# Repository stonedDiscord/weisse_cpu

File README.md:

# Die Weiße CPU

Dies ist ein Reverse-Engineering Projekt fuer die "Elektronische Steuereinheit" von adp.

```mermaid
graph LR
    4087-000101

    subgraph CPU_BLK["CPU"]
        C["8085A\nICB2\n74LS373 addr latch\n74LS245 data buf"]
    end

    subgraph ADEC["Address Decode"]
        D["74LS138 (ICH5)\nmem bank select\n\n74LS42 ×3\nI/O port select"]
    end

    subgraph MMAP["Memory Map"]
        M1["0x0000–0x3FFF\nSocket 1 · ICD6 27128  (16 KB)"]
        M2["0x4000–0x7FFF\nSocket 2 · ICE6 27128  (16 KB)"]
        M3["0x8000–0x8FFF\nSocket 3 · ICC5 2764  (8 KB, empty)"]
        M4["0x9000–0x900F\nRTC · ICA3 HD146818  (16 B, mem-mapped)"]
        M5["0xC000–0xFFFF\nSRAM · ICC6 CY62256  (32 KB chip)"]
    end

    subgraph IOMAP["I/O Map"]
        I1["0x50  8279 data\n0x51  8279 cmd"]
        I2["0x60–6F  8256 regs"]
        I3["0x70  coin ejector\n0x71  sound start\n0x72  tone note\n0x73  PPI ctrl"]
    end

    subgraph EXT["External"]
        E1["16× 7-seg display\nLamp matrix 8×8\nButton/coin matrix 8×8"]
        E2["Serial 4800 8N1\nreel stepper motor\nreel optical sensor"]
        E3["Coin ejector\nTone generator"]
    end

    C <--> D
    D <--> MMAP
    D <--> IOMAP
    I1 --- E1
    I2 --- E2
    I3 --- E3
```

Bei 4040 Platinen sind die IO Adressen anders verteilt:

| IO | Ports |
| ---- | ----------------|
| 0x70-0x73 | 8255: Auswerfer+Zähler+Sound |
| 0x80-0x81 | 8279: Lampen+Tasten |
| 0x90-0x9f | 8256: Timer+Seriell+Walzen |

Aus diesem Grund sind die Programme nicht mit beiden Platinen kompatibel.
Die Lampen und Timer würden ohne Anpassung nicht funktionieren.

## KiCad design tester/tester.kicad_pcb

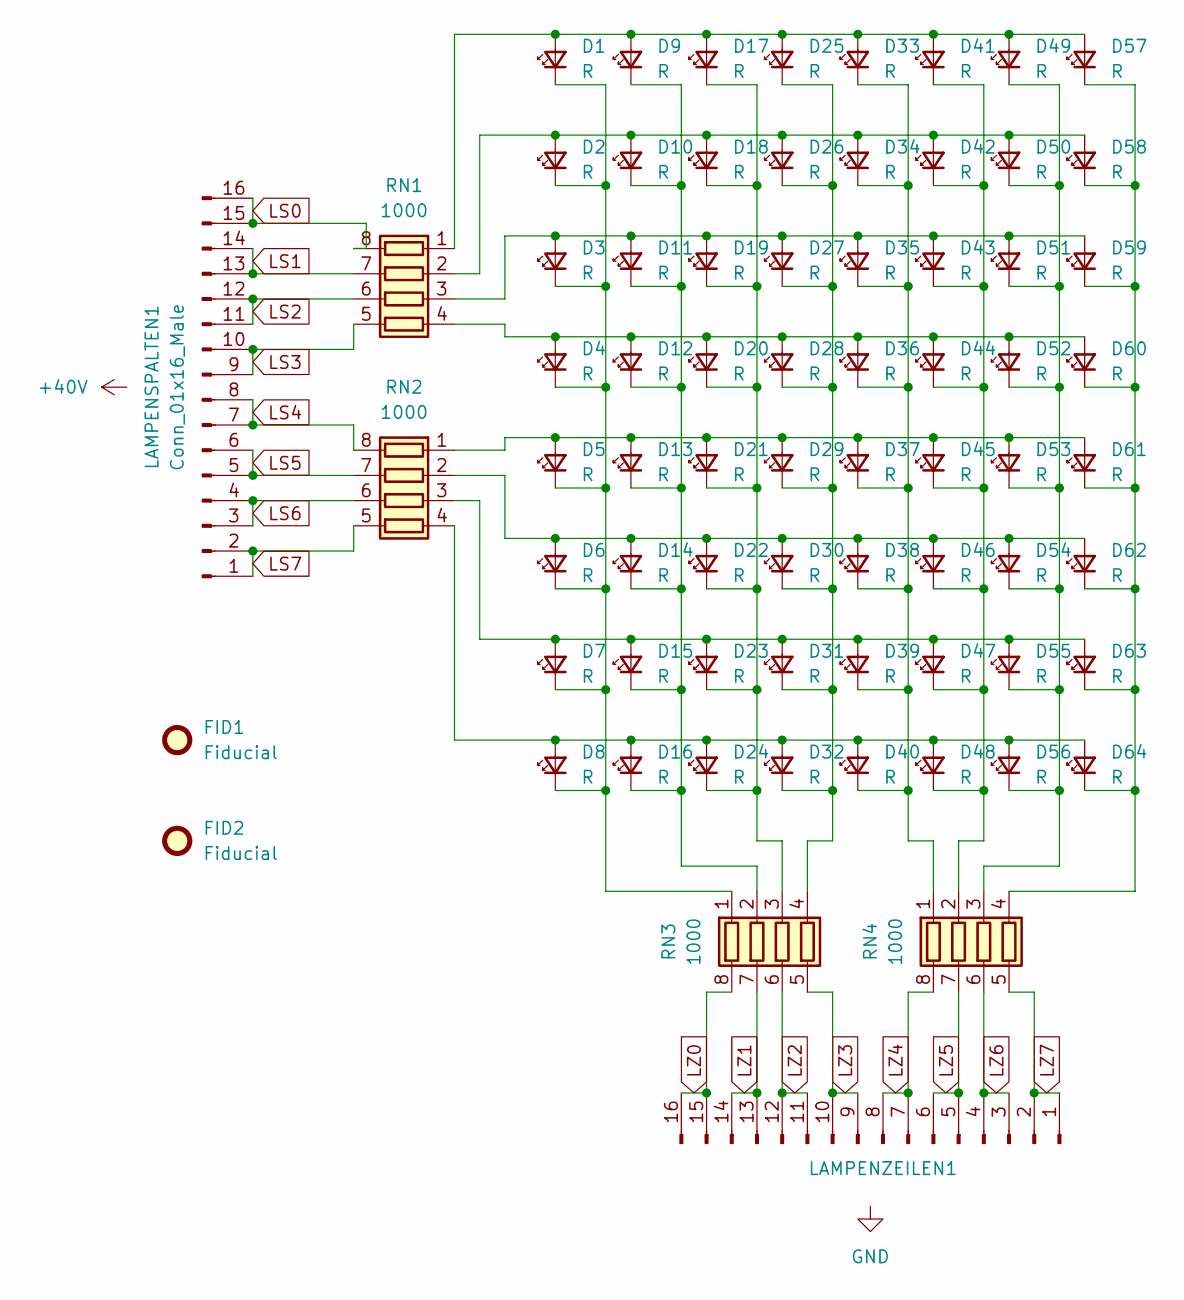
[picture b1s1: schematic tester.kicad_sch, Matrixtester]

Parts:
D1, D2, D3, D4, D5, D6, D7, D8, D9, D10, D11, D12, D13, D14, D15, D16, D17, D18, D19, D20, D21, D22, D23, D24, D25, D26, D27, D28, D29, D30, D31, D32, D33, D34, D35, D36, D37, D38, D39, D40, D41, D42, D43, D44, D45, D46, D47, D48, D49, D50, D51, D52, D53, D54, D55, D56, D57, D58, D59, D60, D61, D62, D63, D64: R; LED_0603_1608Metric_Pad1.05x0.95mm_HandSolder
FID1: Fiducial; Fiducial_Cross_1.5mm_Mask2mm
FID2: Fiducial; Fiducial_0.5mm_Mask1.5mm
LAMPENSPALTEN1: Conn_01x16_Male; Lumberg_MSF_B16B-MSF-A_1x16_P2.50mm_Vertical
LAMPENZEILEN1: Conn_01x16_Pin; Lumberg_MSF_B16B-MSF-A_1x16_P2.50mm_Vertical
RN1, RN2, RN3, RN4: 1000; R_Array_Concave_4x0603

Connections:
LS0: LAMPENSPALTEN1.15, LAMPENSPALTEN1.16, RN1.8 (R1.2)
LS1: LAMPENSPALTEN1.13, LAMPENSPALTEN1.14, RN1.7 (R2.2)
LS2: LAMPENSPALTEN1.11, LAMPENSPALTEN1.12, RN1.6 (R3.2)
LS3: LAMPENSPALTEN1.9, LAMPENSPALTEN1.10, RN1.5 (R4.2)
LS4: LAMPENSPALTEN1.7, LAMPENSPALTEN1.8, RN2.8 (R1.2)
LS5: LAMPENSPALTEN1.5, LAMPENSPALTEN1.6, RN2.7 (R2.2)
LS6: LAMPENSPALTEN1.3, LAMPENSPALTEN1.4, RN2.6 (R3.2)
LS7: LAMPENSPALTEN1.1, LAMPENSPALTEN1.2, RN2.5 (R4.2)
LZ0: LAMPENZEILEN1.15, LAMPENZEILEN1.16, RN3.8 (R1.2)
LZ1: LAMPENZEILEN1.13, LAMPENZEILEN1.14, RN3.7 (R2.2)
LZ2: LAMPENZEILEN1.11, LAMPENZEILEN1.12, RN3.6 (R3.2)
LZ3: LAMPENZEILEN1.9, LAMPENZEILEN1.10, RN3.5 (R4.2)
LZ4: LAMPENZEILEN1.7, LAMPENZEILEN1.8, RN4.8 (R1.2)
LZ5: LAMPENZEILEN1.5, LAMPENZEILEN1.6, RN4.7 (R2.2)
LZ6: LAMPENZEILEN1.3, LAMPENZEILEN1.4, RN4.6 (R3.2)
LZ7: LAMPENZEILEN1.1, LAMPENZEILEN1.2, RN4.5 (R4.2)
unnamed: D1.2 (A), D9.2 (A), D17.2 (A), D25.2 (A), D33.2 (A), D41.2 (A), D49.2 (A), D57.2 (A), RN1.1 (R1.1)
unnamed: D1.1 (K), D2.1 (K), D3.1 (K), D4.1 (K), D5.1 (K), D6.1 (K), D7.1 (K), D8.1 (K), RN3.1 (R1.1)
unnamed: D2.2 (A), D10.2 (A), D18.2 (A), D26.2 (A), D34.2 (A), D42.2 (A), D50.2 (A), D58.2 (A), RN1.2 (R2.1)
unnamed: D9.1 (K), D10.1 (K), D11.1 (K), D12.1 (K), D13.1 (K), D14.1 (K), D15.1 (K), D16.1 (K), RN3.2 (R2.1)
unnamed: D3.2 (A), D11.2 (A), D19.2 (A), D27.2 (A), D35.2 (A), D43.2 (A), D51.2 (A), D59.2 (A), RN1.3 (R3.1)
unnamed: D4.2 (A), D12.2 (A), D20.2 (A), D28.2 (A), D36.2 (A), D44.2 (A), D52.2 (A), D60.2 (A), RN1.4 (R4.1)
unnamed: D5.2 (A), D13.2 (A), D21.2 (A), D29.2 (A), D37.2 (A), D45.2 (A), D53.2 (A), D61.2 (A), RN2.1 (R1.1)
unnamed: D6.2 (A), D14.2 (A), D22.2 (A), D30.2 (A), D38.2 (A), D46.2 (A), D54.2 (A), D62.2 (A), RN2.2 (R2.1)
unnamed: D7.2 (A), D15.2 (A), D23.2 (A), D31.2 (A), D39.2 (A), D47.2 (A), D55.2 (A), D63.2 (A), RN2.3 (R3.1)
unnamed: D8.2 (A), D16.2 (A), D24.2 (A), D32.2 (A), D40.2 (A), D48.2 (A), D56.2 (A), D64.2 (A), RN2.4 (R4.1)
unnamed: D17.1 (K), D18.1 (K), D19.1 (K), D20.1 (K), D21.1 (K), D22.1 (K), D23.1 (K), D24.1 (K), RN3.3 (R3.1)
unnamed: D25.1 (K), D26.1 (K), D27.1 (K), D28.1 (K), D29.1 (K), D30.1 (K), D31.1 (K), D32.1 (K), RN3.4 (R4.1)
unnamed: D33.1 (K), D34.1 (K), D35.1 (K), D36.1 (K), D37.1 (K), D38.1 (K), D39.1 (K), D40.1 (K), RN4.1 (R1.1)
unnamed: D41.1 (K), D42.1 (K), D43.1 (K), D44.1 (K), D45.1 (K), D46.1 (K), D47.1 (K), D48.1 (K), RN4.2 (R2.1)
unnamed: D49.1 (K), D50.1 (K), D51.1 (K), D52.1 (K), D53.1 (K), D54.1 (K), D55.1 (K), D56.1 (K), RN4.3 (R3.1)
unnamed: D57.1 (K), D58.1 (K), D59.1 (K), D60.1 (K), D61.1 (K), D62.1 (K), D63.1 (K), D64.1 (K), RN4.4 (R4.1)

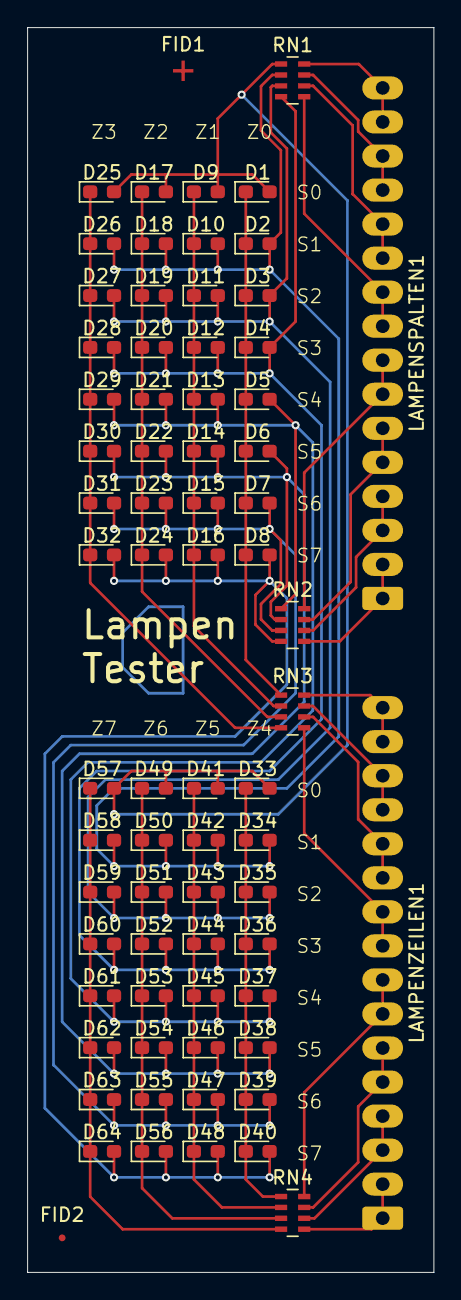
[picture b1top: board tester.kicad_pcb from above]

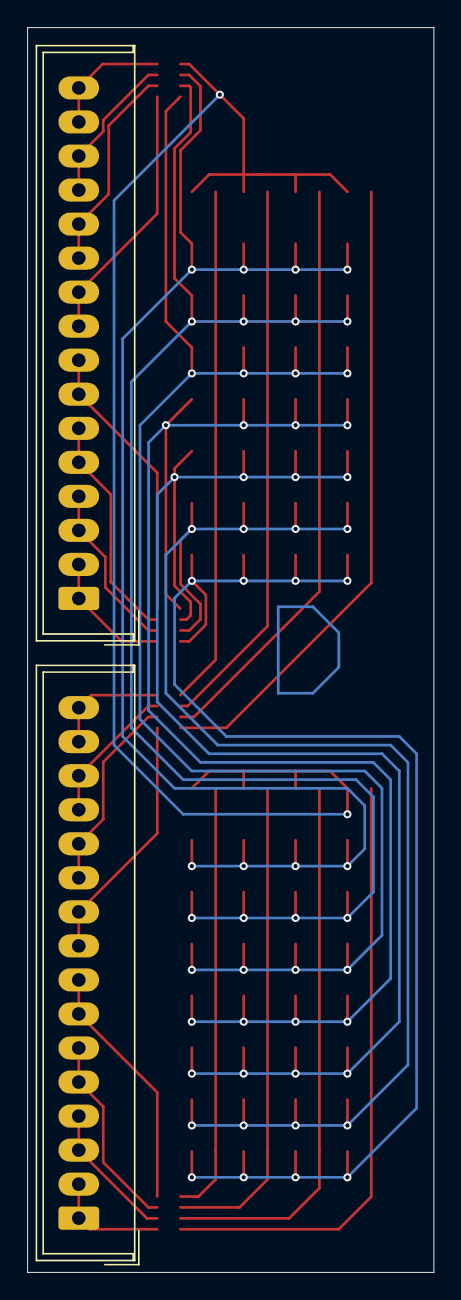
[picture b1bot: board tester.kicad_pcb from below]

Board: 2 copper layers, 29.8 x 91.4 mm, 72 parts (2 on the bottom side), 32 nets.

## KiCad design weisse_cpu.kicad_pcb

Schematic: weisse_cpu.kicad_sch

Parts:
AUSWERFER+SPERRMAG1: Conn_01x06_Pin; PinHeader_1x06_P2.54mm_Vertical
BATTERIE2: Battery_Cell; Batterie
C1, C76, C110, C130, C131, C159, C160, C161: C; C_Rect_L9.0mm_W2.5mm_P7.50mm_MKT
C2, C3, C49: C; CP_Radial_Tantal_D4.5mm_P2.50mm
C4, C5, C6, C7, C8, C9, C10, C11, C143, C144, C145, C146, C147, C148, C149, C150, C151, C152, C153, C154, C155, C156, C157, C158: C; C_Axial_L3.8mm_D2.6mm_P7.50mm_Horizontal
C20, C21, C22, C23, C24, C25, C26, C27: C; C_Rect_L7.0mm_W2.0mm_P5.00mm
C48: C; CP_Radial_Tantal_D4.5mm_P5.00mm
D1, D2, D4, D5, D6, D7, D8, D10, D11, D12, D13, D14, D15, D16, D17, D18, D19, D25, D26, D28, D29, D50, D51, D52, D73, D74, D75, D76, D77, D78, D79, D80, D81, D82, D83, D84, D85, D86, D87, D88, D89, D90, D91, D92, D93, D94, D95, D96, D97, D98, D99, D100, D101, D102, D103, D104, D105, D106, D107, D108, D109, D110, D111, D112: D; D_A-405_P7.62mm_Horizontal
D3, D27: D; BigDiode
DM1, DM2: DAN_801; SIP9_Housing
EINGAENGE1: Conn_01x08_Male; PinHeader_1x08_P2.54mm_Vertical
GONG1: Conn_01x02_Pin; PinHeader_1x02_P2.54mm_Vertical; not fitted
ICA2: LM324; DIP-14_W7.62mm
ICA3: PAL20L8; DIP-24_W15.24mm
ICA7: 4066; DIP-14_W7.62mm
ICA8: 40106; DIP-14_W7.62mm
ICA9: CNY17-1; DIP-6_W7.62mm
ICB2: 8085; DIP-40_W15.24mm
ICB4: 74LS245; DIP-20_W7.62mm
ICB5: 74LS373; DIP-20_W7.62mm
ICB8: ICM7555xP; DIP-8_W7.62mm
ICB9, ICB10: 4066; DIP-14_W7.62mm
ICC3: 74LS04; DIP-14_W7.62mm
ICC4: 74LS00; DIP-14_W7.62mm
ICC5: 2764; DIP-24_W15.24mm
ICC6: CXK5816PN-12L; DIP-24_W15.24mm
ICC8: 74LS42; DIP-16_W7.62mm
ICC10: 4066; DIP-14_W7.62mm
ICD3: 74LS257; DIP-16_W7.62mm
ICD4: 74LS244; DIP-20_W7.62mm
ICD6: 27128; DIP-28_W15.24mm
ICD8: CD4051B; DIP-16_W7.62mm
ICD10: 4066; DIP-14_W7.62mm
ICE2: 8256; DIP-40_W15.24mm
ICE4: 74125; DIP-14_W7.62mm
ICE5: 74LS42; DIP-16_W7.62mm
ICE6: 27128; DIP-28_W15.24mm
ICE10: 4066; DIP-14_W7.62mm
ICF2: LM324; DIP-14_W7.62mm
ICF3: 4028; DIP-16_W7.62mm
ICF4-2: 4013; DIP-14_W7.62mm
ICF5: 74LS42; DIP-16_W7.62mm
ICF8: CD4051B; DIP-16_W7.62mm
ICF10: 4066; DIP-14_W7.62mm
ICG1, ICG2, ICG4, ICG4-1: LM324; DIP-14_W7.62mm
ICG3: 4051; DIP-16_W7.62mm
ICG5: DIP-40_W15.24mm
ICG8-1: 74LS290; DIP-14_W7.62mm
ICG8-2: 4040; DIP-16_W7.62mm
ICG9: DIP-16_W7.62mm
ICG10-1, ICG10-2: 4066; DIP-14_W7.62mm
ICH1: 4098; DIP-16_W7.62mm
ICH2: LM324; DIP-14_W7.62mm
ICH3: 4040; DIP-16_W7.62mm
ICH4-1: ULN2004A; DIP-16_W7.62mm
ICH4-2: 4520; DIP-16_W7.62mm
ICH5: 74LS138; DIP-16_W7.62mm
ICH6: 74AHC273; DIP-20_W7.62mm
ICH8: CD74HC4067M; SOIC-24W_7.5x15.4mm_P1.27mm
ICH10: 4066; DIP-14_W7.62mm
ICJ5, ICJ6: 74AHC273; DIP-20_W7.62mm
ICK4: 4013; DIP-14_W7.62mm
ICK5, ICK6, ICK7, ICK8, ICK11: LM324; DIP-14_W7.62mm
ICL4, ICL6, ICL9: 4093; DIP-14_W7.62mm
ICL5, ICL7: LM324; DIP-14_W7.62mm
ICL8: 4013; DIP-14_W7.62mm
ICL10: NE556; DIP-14_W7.62mm
ICL11: Opamp_Quad; DIP-14_W7.62mm
LAMPENSPALTEN1: Conn_01x16_Male; PinHeader_1x16_P2.54mm_Vertical
LAMPENZEILEN1: Conn_01x16_Pin; PinHeader_1x16_P2.54mm_Vertical
LAUTSPRECHER1: Conn_01x06_Pin; PinHeader_1x06_P2.54mm_Vertical
LED1, LED2, LED3, LED4, LED5: LED; LED_D5.0mm
LEISTUNGSAUSGAENGE1: Conn_01x10_Pin; PinHeader_1x10_P2.54mm_Vertical; not fitted
LEISTUNGSNETZ1: Conn_01x08_Male; PinHeader_1x08_P2.54mm_Vertical
LEUCHTZIFFERNANZEIGE1: Conn_01x12_Pin; PinHeader_1x12_P2.54mm_Vertical
MATRIX-EINGAENGE1: Conn_01x06_Pin; PinHeader_1x06_P2.54mm_Vertical; not fitted
MUENZANNAHME1: Conn_01x20_Pin; PinHeader_1x20_P2.54mm_Vertical
Q1: Crystal; Crystal_AT310_D3.0mm_L10.0mm_Vertical
Q2: Crystal; Crystal_HC18-U_Vertical
R1, R2, R10, R11, R12, R13, R27, R28, R29: 1,2k 5%; R_Axial_DIN0414_L11.9mm_D4.5mm_P20.32mm_Horizontal
R3, R17: R; R_Axial_DIN0204_L3.6mm_D1.6mm_P7.62mm_Horizontal
R4, R5, R6, R7: R; R_Axial_DIN0207_L6.3mm_D2.5mm_P10.16mm_Horizontal
R15, R20, R21, R123: 1 kΩ ±5%; R_Axial_DIN0207_L6.3mm_D2.5mm_P10.16mm_Horizontal
R16, R86, R150: 100 kΩ ±5%; R_Axial_DIN0207_L6.3mm_D2.5mm_P10.16mm_Horizontal
R22, R84, R124: 10 kΩ ±5%; R_Axial_DIN0207_L6.3mm_D2.5mm_P10.16mm_Horizontal
R23: 320 kΩ ±5%; R_Axial_DIN0207_L6.3mm_D2.5mm_P10.16mm_Horizontal
R40: 15 2%; BigResistor
R41, R65, R66, R90, R100: R; BigResistor
R82: 3 kΩ ±5%; R_Axial_DIN0207_L6.3mm_D2.5mm_P10.16mm_Horizontal
R83: 180 Ω ±5%; R_Axial_DIN0207_L6.3mm_D2.5mm_P10.16mm_Horizontal
R85: 27 kΩ ±5%; R_Axial_DIN0207_L6.3mm_D2.5mm_P10.16mm_Horizontal
R121: 220 kΩ ±5%; R_Axial_DIN0207_L6.3mm_D2.5mm_P10.16mm_Horizontal
R122: 1 MΩ ±5%; R_Axial_DIN0207_L6.3mm_D2.5mm_P10.16mm_Horizontal
R129: 1 kΩ ±5%; R_Axial_DIN0309_L9.0mm_D3.2mm_P15.24mm_Horizontal
R130: 51; R_Axial_DIN0414_L11.9mm_D4.5mm_P20.32mm_Horizontal
R135: 100 ±5%; R_Axial_DIN0414_L11.9mm_D4.5mm_P20.32mm_Horizontal
R136, R137: 200 Ω ±5%; R_Axial_DIN0414_L11.9mm_D4.5mm_P20.32mm_Horizontal
R140: 220 Ω ±5%; R_Axial_DIN0207_L6.3mm_D2.5mm_P10.16mm_Horizontal
R148: 3,3M 5%; R_Axial_DIN0207_L6.3mm_D2.5mm_P10.16mm_Horizontal
RM2, RM20: R_Network04; R_Array_SIP5
RM3, RM5, RM7, RM11, RM12, RM13, RM21, RM50, RM56, RM57, RM58, RM66, RM80, RM82, RM84: R_Network08; R_Array_SIP9
RM4, RM6, RM8, RM10, RM81, RM83, RM85: R_Pack08; DIP-16_W7.62mm
RN1: R_Network08; R_Array_SIP9
SERIELLE_DATEN1: Conn_01x08_Pin; PinHeader_1x08_P2.54mm_Vertical
SERVICEANZEIGE+TASTATUR1: Conn_01x20_Male; PinHeader_1x20_P2.54mm_Vertical
SIGNALNETZ1: Conn_01x06_Male; PinHeader_1x06_P2.54mm_Vertical
SW1: SW_DIP_x04; SW_DIP_SPSTx04_Slide_9.78x12.34mm_W7.62mm_P2.54mm
TASTEN1: Conn_01x06_Pin; PinHeader_1x06_P2.54mm_Vertical
TR1, TR2, TR10, TR11, TR12, TR25, TR26: BDX34B; TO-220-3_Vertical
TR3, TR14, TR15, TR16, TR30, TR31, TR33, TR34, TR85: BC237; TO-92_Inline
TR13: BDX54C; TO-220-3_Vertical
TR27: BD140; TO-126-3_Vertical
TR29, TR65, TR66: BD139; TO-126-3_Vertical
TR32: BD679; TO-126-3_Vertical
TR40: BC557; TO-92_Inline
TR55, TR56, TR70, TR71, TR72, TR73, TR80, TR81, TR82, TR83, TR95, TR96, TR97: Q_NPN_Darlington_BCE; TO-220-3_Vertical
TR84, TR87: NMOS; BigTransistor
TR86: BC327; TO-92_Inline
TUERSCHALTER+SPIELZAEHLER1: Conn_01x04_Pin; PinHeader_1x04_P2.54mm_Vertical
TY1, TY2, TY5, TY6, TY7, TY8, TY15, TY16: TIC126; TO-220-3_Vertical
WALZENANSTEUERUNG1: Conn_01x20_Pin; PinHeader_1x20_P2.54mm_Vertical
ZUSATZTASTEN1: Conn_01x08_Pin; PinHeader_1x08_P2.54mm_Vertical
ZUSATZWALZEN1: Conn_01x12_Pin; PinHeader_1x12_P2.54mm_Vertical; not fitted

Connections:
+5V: LEUCHTZIFFERNANZEIGE1.3, SERIELLE_DATEN1.1, SERVICEANZEIGE+TASTATUR1.2, SIGNALNETZ1.5, SIGNALNETZ1.6
+12V: C161.1, EINGAENGE1.1, LAUTSPRECHER1.2, LEUCHTZIFFERNANZEIGE1.4, MUENZANNAHME1.4, SERIELLE_DATEN1.8, SIGNALNETZ1.4, TASTEN1.6, TUERSCHALTER+SPIELZAEHLER1.3, ZUSATZTASTEN1.2
+15V: SIGNALNETZ1.3
+24V: LAUTSPRECHER1.1, LEISTUNGSAUSGAENGE1.10, LEISTUNGSNETZ1.4, LEISTUNGSNETZ1.5, MUENZANNAHME1.2, SERIELLE_DATEN1.4, WALZENANSTEUERUNG1.12
+48V: AUSWERFER+SPERRMAG1.1, EINGAENGE1.6, GONG1.1, LEISTUNGSNETZ1.6, LEISTUNGSNETZ1.7, LEISTUNGSNETZ1.8, R40.2, SERIELLE_DATEN1.2, TUERSCHALTER+SPIELZAEHLER1.4, WALZENANSTEUERUNG1.14
A0: ICB5.2 (O0), ICC5.8 (A0), ICC6.8 (A0), ICD6.10 (A0), ICE6.10 (A0), RM58.9 (R8)
A1: ICB5.5 (O1), ICC5.7 (A1), ICC6.7 (A1), ICD6.9 (A1), ICE6.9 (A1), RM58.8 (R7)
A2: ICB5.6 (O2), ICC5.6 (A2), ICC6.6 (A2), ICD6.8 (A2), ICE6.8 (A2), RM58.7 (R6)
A3: ICB5.9 (O3), ICC5.5 (A3), ICC6.5 (A3), ICD6.7 (A3), ICE6.7 (A3), RM58.6 (R5)
A4: ICB5.12 (O4), ICC5.4 (A4), ICC6.4 (A4), ICD6.6 (A4), ICE6.6 (A4), RM58.5 (R4)
A5: ICB5.15 (O5), ICC5.3 (A5), ICC6.3 (A5), ICD6.5 (A5), ICE6.5 (A5), RM58.4 (R3)
A6: ICB5.16 (O6), ICC5.2 (A6), ICC6.2 (A6), ICD6.4 (A6), ICE6.4 (A6), RM58.3 (R2)
A7: ICB5.19 (O7), ICC5.1 (A7), ICC6.1 (A7), ICD6.3 (A7), ICE6.3 (A7), RM58.2 (R1)
A8: ICC5.23 (A8), ICC6.23 (A8), ICD6.25 (A8), ICE6.25 (A8), RM57.2 (R1)
A9: ICC5.22 (A9), ICC6.22 (A9), ICD6.24 (A9), ICE6.24 (A9), RM57.3 (R2)
A10: ICC5.19 (A10), ICC6.19 (A10), ICD6.21 (A10), ICE6.21 (A10), RM57.6 (R5)
A11: ICC5.21 (A11), ICD6.23 (A11), ICE6.23 (A11), RM57.4 (R3)
A12: ICD6.2 (A12), ICE6.2 (A12)
A13: ICD6.26 (A13), ICE6.26 (A13)
AD0: ICB2.12 (AD0), ICB4.2 (A0), ICB5.3 (D0)
AD1: ICB2.13 (AD1), ICB4.3 (A1), ICB5.4 (D1)
AD2: ICB2.14 (AD2), ICB4.4 (A2), ICB5.7 (D2)
AD3: ICB2.15 (AD3), ICB4.5 (A3), ICB5.8 (D3)
AD4: ICB2.16 (AD4), ICB4.6 (A4), ICB5.13 (D4)
AD5: ICB2.17 (AD5), ICB4.7 (A5), ICB5.14 (D5)
AD6: ICB2.18 (AD6), ICB4.8 (A6), ICB5.17 (D6)
AD7: ICB2.19 (AD7), ICB4.9 (A7), ICB5.18 (D7)
D0: ICB4.18 (B0), ICC5.9 (D0), ICC6.9 (I/O1), ICD6.11 (D0), ICE6.11 (D0), ICG5.12 (DB0)
D1: ICB4.17 (B1), ICC5.10 (D1), ICC6.10 (I/O2), ICD6.12 (D1), ICE6.12 (D1), ICG5.13 (DB1)
D2: ICB4.16 (B2), ICC5.11 (D2), ICC6.11 (I/O3), ICD6.13 (D2), ICE6.13 (D2), ICG5.14 (DB2)
D3: ICB4.15 (B3), ICC5.13 (D3), ICC6.13 (I/O4), ICD6.15 (D3), ICE6.15 (D3), ICG5.15 (DB3)
D4: ICB4.14 (B4), ICC5.14 (D4), ICC6.14 (I/O5), ICD6.16 (D4), ICE6.16 (D4), ICG5.16 (DB4), RM57.5 (R4)
D5: ICB4.13 (B5), ICC5.15 (D5), ICC6.15 (I/O6), ICD6.17 (D5), ICE6.17 (D5), ICG5.17 (DB5), RM57.7 (R6)
D6: ICB4.12 (B6), ICC5.16 (D6), ICC6.16 (I/O7), ICD6.18 (D6), ICE6.18 (D6), ICG5.18 (DB6), RM57.9 (R8)
D7: ICB4.11 (B7), ICC5.17 (D7), ICC6.17 (I/O8), ICD6.19 (D7), ICE6.19 (D7), ICG5.19 (DB7), RM57.8 (R7)
GND: C159.2, C160.2, C161.2, D73.1 (K), D74.1 (K), D75.1 (K), D76.1 (K), D77.1 (K), D78.1 (K), D79.1 (K), D80.1 (K), EINGAENGE1.7, ICB5.10 (GND), ICB9.7 (VSS), ICB10.7 (VSS), ICC3.7 (GND), ICC4.7 (GND), ICC6.12 (GND), ICC10.7 (VSS), ICD3.8 (GND), ICD6.14 (GND), ICD10.7 (VSS), ICE6.14 (GND), ICE10.7 (VSS), ICF10.7 (VSS), ICG5.20 (Vss), ICG8-1.7 (GND), ICG8-2.8 (VSS), ICG9.1 (Vss), ICG10-1.14 (VDD), ICG10-2.7 (VSS), ICH1.8 (VSS), ICH8.12 (GND), ICH10.7 (VSS), ICK11.11 (V-), ICL8.7 (VSS), ICL9.5, ICL9.6, ICL9.7 (Vss), ICL10.7 (GND), LEUCHTZIFFERNANZEIGE1.1, R137.1, SERVICEANZEIGE+TASTATUR1.1, SIGNALNETZ1.1, SIGNALNETZ1.2, WALZENANSTEUERUNG1.1, ZUSATZTASTEN1.1
GNDPWR: LAUTSPRECHER1.4, LEISTUNGSAUSGAENGE1.2, LEISTUNGSNETZ1.1, LEISTUNGSNETZ1.2, LEISTUNGSNETZ1.3, MUENZANNAHME1.1, R41.2, R65.1, R66.1, R90.2, R100.1, SERIELLE_DATEN1.7, WALZENANSTEUERUNG1.13
unnamed: C76.2, R82.1, R83.1
unnamed: D1.2 (A), D2.2 (A), D10.2 (A), D11.2 (A), D12.2 (A), D13.2 (A), D25.2 (A), D26.2 (A)
unnamed: D1.1 (K), D2.1 (K), D10.1 (K), D11.1 (K), D12.1 (K), D13.1 (K), D25.1 (K), D26.1 (K), R40.1, RN1.1 (common), TR1.3 (E), TR2.3 (E), TR10.3 (E), TR11.3 (E), TR12.3 (E), TR13.3 (E), TR25.3 (E), TR26.3 (E)
unnamed: D4.2 (A), LAMPENZEILEN1.15, LAMPENZEILEN1.16, TY1.2 (A)
unnamed: D5.2 (A), LAMPENZEILEN1.13, LAMPENZEILEN1.14, TY2.2 (A)
unnamed: C4.2, C5.2, C6.2, C7.2, C8.2, C9.2, C10.2, C11.2, D6.2 (A)
unnamed: D6.1 (K), R4.2
unnamed: D7.2 (A), ICA2.3 (+), R148.1
unnamed: D8.2 (A), LED4.2 (A)
unnamed: D14.2 (A), LAMPENZEILEN1.11, LAMPENZEILEN1.12, TY5.2 (A)
unnamed: D4.1 (K), D5.1 (K), D14.1 (K), D15.1 (K), D16.1 (K), D17.1 (K), D28.1 (K), D29.1 (K), TR29.2 (C)
unnamed: D15.2 (A), LAMPENZEILEN1.9, LAMPENZEILEN1.10, TY6.2 (A)
unnamed: D16.2 (A), LAMPENZEILEN1.7, LAMPENZEILEN1.8, TY7.2 (A)
unnamed: D17.2 (A), LAMPENZEILEN1.5, LAMPENZEILEN1.6, TY8.2 (A)
unnamed: D18.2 (A), R16.2
unnamed: D3.1 (K), D27.1 (K), TR29.1 (E)
unnamed: D28.2 (A), LAMPENZEILEN1.3, LAMPENZEILEN1.4, TY15.2 (A)
unnamed: D29.2 (A), LAMPENZEILEN1.1, LAMPENZEILEN1.2, TY16.2 (A)
unnamed: D50.2 (A), R41.1, TR55.3 (E), TR56.3 (E)
unnamed: D51.2 (A), TR65.3 (B)
unnamed: D52.2 (A), TR66.3 (B)
unnamed: D85.1 (K), D86.1 (K), D87.1 (K), D88.1 (K)
unnamed: D89.1 (K), D90.1 (K), D91.1 (K), D92.1 (K), D93.1 (K), D94.1 (K), D95.1 (K), D96.1 (K)
unnamed: D97.1 (K), D98.1 (K), D99.1 (K), D100.1 (K), D102.1 (K), D103.1 (K), D104.1 (K)
unnamed: D105.1 (K), D106.1 (K), D107.1 (K), D108.1 (K), D110.1 (K), D111.1 (K)
unnamed: ICA2.5 (+), R148.2
unnamed: ICB2.1 (X1), R20.1
unnamed: ICC4.3, ICC4.4, ICC4.5
unnamed: ICE2.32 (P1.7), RM11.3 (R2)
unnamed: ICE2.31 (P2.0), RM11.4 (R3)
unnamed: ICE2.30 (P2.1), RM11.5 (R4)
unnamed: ICE2.29 (P2.2), RM21.2 (R1)
unnamed: ICE2.28 (P2.3), RM21.3 (R2)
unnamed: ICE2.27 (P2.4), RM21.4 (R3)
unnamed: ICE2.26 (P2.5), RM21.5 (R4)
unnamed: ICE2.25 (P2.6), RM21.6 (R5)
unnamed: ICE2.24 (P2.7), RM21.7 (R6)
unnamed: ICF2.14, R4.1
unnamed: ICF2.3 (+), RM11.6 (R5)
unnamed: ICF2.2 (-), ICF2.6 (-)
unnamed: ICF2.5 (+), RM11.7 (R6)
unnamed: ICG1.2 (-), ICG1.6 (-), ICG2.2 (-), ICG2.6 (-)
unnamed: ICG4.2 (-), ICG4.6 (-)
unnamed: ICG4.10 (+), ICG5.29 (OUT_B2)
unnamed: ICG9.15 (÷_239), ICH8.8 (I1)
unnamed: ICG9.14 (÷_253), ICH8.7 (I2)
unnamed: ICG9.13 (÷_268), ICH8.6 (I3)
unnamed: ICG9.12 (÷_284), ICH8.5 (I4)
unnamed: ICG9.11 (÷_301), ICH8.4 (I5)
unnamed: ICG9.10 (÷_319), ICH8.3 (I6)
unnamed: ICG9.9 (÷_338), ICH8.2 (I7)
unnamed: ICG9.8 (÷_358), ICH8.23 (I8)
unnamed: ICG9.7 (÷_379), ICH8.22 (I9)
unnamed: ICG9.6 (÷_402), ICH8.21 (I10)
unnamed: ICG9.5 (÷_426), ICH8.20 (I11)
unnamed: ICG9.4 (÷_451), ICH8.19 (I12)
unnamed: ICG9.16 (÷_478), ICH8.9 (I0)
unnamed: ICH4-1.16 (O1), R2.1
unnamed: ICH4-1.15 (O2), R10.1
unnamed: ICH4-1.14 (O3), R11.1
unnamed: ICH4-1.13 (O4), R12.1
unnamed: ICH4-1.12 (O5), R13.1
unnamed: ICH4-1.11 (O6), R27.1
unnamed: ICH4-1.10 (O7), R28.1
unnamed: ICH6.5 (Q1), RM56.4 (R3)
unnamed: ICH6.6 (Q2), RM56.3 (R2)
unnamed: ICH6.9 (Q3), RM56.2 (R1)
unnamed: ICL9.8, ICL9.9
unnamed: ICL10.2 (THR), ICL10.6 (TR)
unnamed: ICL11.10 (+), ICL11.12 (+)
unnamed: LAMPENSPALTEN1.1, LAMPENSPALTEN1.2, TR26.2 (C)
unnamed: LAMPENSPALTEN1.3, LAMPENSPALTEN1.4, TR25.2 (C)
unnamed: LAMPENSPALTEN1.5, LAMPENSPALTEN1.6, TR13.2 (C)
unnamed: LAMPENSPALTEN1.7, LAMPENSPALTEN1.8, TR12.2 (C)
unnamed: LAMPENSPALTEN1.9, LAMPENSPALTEN1.10, TR11.2 (C)
unnamed: LAMPENSPALTEN1.11, LAMPENSPALTEN1.12, TR10.2 (C)
unnamed: LAMPENSPALTEN1.13, LAMPENSPALTEN1.14, TR2.2 (C)
unnamed: LAMPENSPALTEN1.15, LAMPENSPALTEN1.16, TR1.2 (C)
unnamed: LED4.1 (K), R82.2
unnamed: LED5.1 (K), R140.2
unnamed: MUENZANNAHME1.6, RM83.8 (R8.1)
unnamed: MUENZANNAHME1.7, RM83.7 (R7.1)
unnamed: MUENZANNAHME1.8, RM83.6 (R6.1)
unnamed: MUENZANNAHME1.9, RM83.5 (R5.1)
unnamed: MUENZANNAHME1.10, RM83.4 (R4.1)
unnamed: MUENZANNAHME1.11, RM83.3 (R3.1)
unnamed: MUENZANNAHME1.12, RM83.2 (R2.1)
unnamed: MUENZANNAHME1.13, RM83.1 (R1.1)
unnamed: MUENZANNAHME1.14, RM85.4 (R4.1)
unnamed: MUENZANNAHME1.15, RM85.5 (R5.1)
unnamed: MUENZANNAHME1.16, RM85.6 (R6.1)
unnamed: MUENZANNAHME1.17, RM85.7 (R7.1)
unnamed: MUENZANNAHME1.18, RM85.8 (R8.1)
unnamed: R22.2, R23.2
unnamed: R84.1, R85.1
unnamed: R135.1, R136.1
unnamed: R136.2, R137.2
unnamed: C5.1, RM3.2 (R1), RM4.15 (R2.2)
unnamed: C6.1, RM3.3 (R2)
unnamed: C7.1, RM3.4 (R3)
unnamed: C8.1, RM3.5 (R4)
unnamed: C11.1, RM3.8 (R7)
unnamed: RM4.14 (R3.2), WALZENANSTEUERUNG1.2
unnamed: RM4.13 (R4.2), WALZENANSTEUERUNG1.3
unnamed: RM4.12 (R5.2), WALZENANSTEUERUNG1.4
unnamed: RM6.2 (R2.1), TASTEN1.1
unnamed: RM6.3 (R3.1), TASTEN1.2
unnamed: RM6.4 (R4.1), TASTEN1.3
unnamed: RM6.5 (R5.1), TASTEN1.4
unnamed: RM8.14 (R3.2), ZUSATZTASTEN1.6
unnamed: RM8.10 (R7.2), ZUSATZTASTEN1.5
unnamed: RM11.9 (R8), RM21.1 (common)
unnamed: DM2.5, R20.2, R21.2, RM13.1 (common)
unnamed: RM81.1 (R1.1), SERVICEANZEIGE+TASTATUR1.10
unnamed: RM81.2 (R2.1), SERVICEANZEIGE+TASTATUR1.9
unnamed: RM81.3 (R3.1), SERVICEANZEIGE+TASTATUR1.8
unnamed: RM81.4 (R4.1), SERVICEANZEIGE+TASTATUR1.7
unnamed: RM81.5 (R5.1), SERVICEANZEIGE+TASTATUR1.11
unnamed: RM81.6 (R6.1), SERVICEANZEIGE+TASTATUR1.12
unnamed: ICG10-1.5, RM81.11 (R6.2)
unnamed: RM81.7 (R7.1), SERVICEANZEIGE+TASTATUR1.13
unnamed: ICG10-1.12, RM81.10 (R7.2)
unnamed: RM81.8 (R8.1), SERVICEANZEIGE+TASTATUR1.14
unnamed: ICG10-1.6, RM81.9 (R8.2)
unnamed: C143.1, RM82.2 (R1)
unnamed: C144.1, RM82.3 (R2)
unnamed: C145.1, RM82.4 (R3)
unnamed: C146.1, RM82.5 (R4)
unnamed: C147.1, RM82.6 (R5)
unnamed: C148.1, RM82.7 (R6)
unnamed: C149.1, RM82.8 (R7)
unnamed: C150.1, RM82.9 (R8)
unnamed: C151.1, RM84.2 (R1)
unnamed: C152.1, RM84.3 (R2)
unnamed: C153.1, RM84.4 (R3)
unnamed: C154.1, RM84.5 (R4)
unnamed: C155.1, RM84.6 (R5)
unnamed: C156.1, RM84.7 (R6)
unnamed: C157.1, RM84.8 (R7)
unnamed: C158.1, RM84.9 (R8)
unnamed: ICK11.1, SERVICEANZEIGE+TASTATUR1.3
unnamed: ICK11.7, SERVICEANZEIGE+TASTATUR1.4
unnamed: R1.2, TR1.1 (B)
unnamed: R2.2, TR2.1 (B)
unnamed: R10.2, TR10.1 (B)
unnamed: R11.2, TR11.1 (B)
unnamed: R12.2, TR12.1 (B)
unnamed: R13.2, TR13.1 (B)
unnamed: R27.2, TR25.1 (B)
unnamed: R28.2, TR26.1 (B)
unnamed: R29.1, TR27.3 (B)
unnamed: R1.1, TR32.2 (C)
unnamed: TR70.3 (E), TR71.3 (E), TR72.3 (E), TR73.3 (E), TR80.3 (E), TR81.3 (E)
unnamed: TR82.3 (E), TR83.3 (E), TR95.3 (E), TR96.3 (E)
unnamed: R123.1, TR84.1 (D)
unnamed: R124.1, TR84.2 (G)
unnamed: R124.2, TR84.3 (S), TR87.3 (S)
unnamed: TY1.1 (K), TY2.1 (K), TY5.1 (K), TY6.1 (K)
unnamed: TY7.1 (K), TY8.1 (K), TY15.1 (K), TY16.1 (K)
unnamed: ICG1.14, WALZENANSTEUERUNG1.15

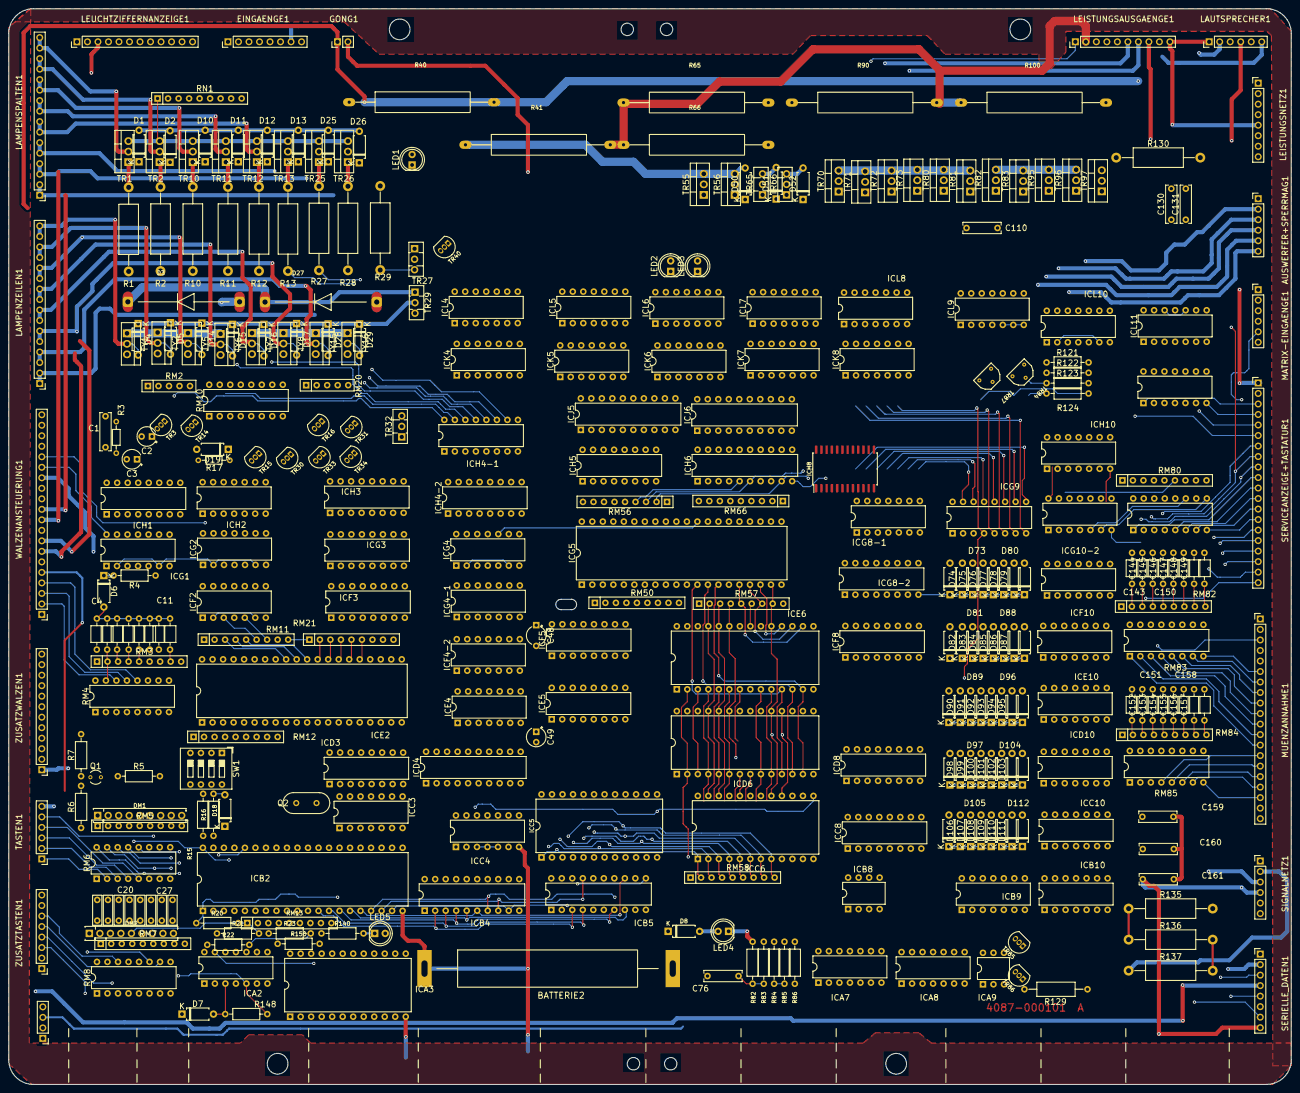
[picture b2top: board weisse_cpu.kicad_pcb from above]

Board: 2 copper layers, 310.0 x 260.0 mm, 325 parts (0 on the bottom side), 196 nets.

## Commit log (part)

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2022-08-11 project file
2022-08-12 lampen ausgänge
2022-08-12 reorganisiere
2022-08-19 footprints und platine
2022-08-19 add a bunch of traces
2022-08-20 serviceabzeige
2023-08-09 draw
2023-08-09 photo
2023-08-09 move transistors down
2023-08-09 move connectors
2023-08-09 move holes
2023-08-10 add eeprom
2023-08-10 new photo and new holes
2023-08-11 mirror board
2023-08-11 hhhhhh
2023-08-11 headers
2023-08-11 mehr anschluss
2023-08-11 rechts
2023-08-11 spin
2023-08-11 3d fix
2023-08-11 3d zoom
2023-08-11 more zoom
2023-08-11 resist
2023-08-11 zoom again
2023-08-11 zoom out
2023-08-11 integer scaling
2023-08-11 corners
2023-08-11 fill got lost again
2023-08-11 schaltplan
2023-08-12 walz
2023-08-12 thyristor
2023-08-12 thryrrristorrr
2023-08-12 batterie
2023-08-13 aaaaaaaa
2023-08-13 suqiggly lines
2023-08-17 muenzen
2023-08-17 logic
2023-08-17 rtx 4060
2023-08-17 transistoren
2023-08-17 caps
2023-08-17 chips
2023-08-17 traces
2023-08-17 lm324
2023-08-17 erthjerghse
2023-08-22 12v cap
2023-09-05 power resistors
2023-09-05 add transistors
2023-09-05 big resistor
2023-09-06 hab vergessen was das war
2023-09-07 schips
2023-09-07 dioden
2023-09-07 diodfen
2023-09-07 resistor packs
2023-09-08 ummmmmmmmmmmmm
2023-09-08 kondensaaa
2023-09-12 neue teile
2023-09-12 aufraeumen
2023-09-12 kibot local
2023-09-12 big one
2023-09-12 jaja
2023-09-13 viiiiel
2023-09-13 batterie und so
2023-09-15 widerstand ist zwecklos
2023-09-16 uiiii
2023-09-19 rrrrrrrrr
2023-09-24 mehr traces
2024-01-19 hhhhhhh
2024-01-23 jjjjjjj
2024-07-09 aaaaaa
2024-08-01 align to grid
2024-08-05 asdas
2024-10-01 zeug
2024-10-07 bringt nix mehr mit aktuellem kicad
2024-10-09 roentgenbild
2024-10-30 verschoben
2024-10-30 hddghr
2024-11-01 fix rom
2024-11-26 tr verschieben
2025-03-26 glaube sound
2025-04-10 text
2025-05-02 linguist override
2025-06-25 rom ram
2025-07-02 sound und rl-sl
2025-07-02 sound runter
2025-07-04 m1a liw in out
2025-07-06 jumper 1/5?
2025-07-12 wd rw
2025-07-12 rst75
2025-07-19 sound data
2025-07-19 rst55
2025-07-23 rnet
2025-07-29 nets
2025-08-07 stecker
2025-08-08 jumper 2
2025-08-11 liw5
2025-08-13 fixes
2025-08-13 del bilder
2025-09-09 lampen tester
2025-09-09 reorg
2025-09-09 halb
2025-09-09 routed
2025-09-09 prod
2025-09-24 led tester
2025-09-25 noten
2025-11-02 move
2025-12-06 courtyard
2025-12-07 segment servicetastatur
2025-12-12 testrom
2025-12-12 switch to z88dk
2025-12-12 outp
2025-12-12 use z80 target
2025-12-12 only int
2025-12-12 out, built
2025-12-12 whitespaces
2025-12-13 schiebung
2025-12-13 io port
2025-12-13 caveman asm
2025-12-13 gnusim syntax
2025-12-13 build script (still fails)
2025-12-13 back to c as no asm available
2025-12-13 leave it at outp now
2025-12-13 gs and as
2025-12-13 jmp sled
2025-12-13 disable ints
2025-12-13 reset
2025-12-14 minipro
2025-12-14 pad and roms folder
2025-12-14 clamp
2025-12-14 20v 40v
2025-12-14 get rid of asxxxx
2025-12-14 c types
2025-12-15 read c
2025-12-15 autogen rom zip
2025-12-15 pretty header
2025-12-15 filter
2025-12-15 add delay
2025-12-15 docs to make my IDE happier
2025-12-15 prep muart
2025-12-15 dump 8256 ports
2025-12-16 tabelle
2025-12-16 dump ports
2025-12-16 orangi
2025-12-16 obvious
2025-12-21 liz in
2025-12-21 ton freq
2025-12-21 sound
2025-12-22 sound def
2025-12-22 boot beep
2025-12-22 display ram
2025-12-22 timing
2025-12-22 overflow
2025-12-22 hhhhh
2025-12-22 bad bad apple
2025-12-22 timer values
2025-12-22 timer simulation
2025-12-22 still bad
2025-12-23 use midi
2025-12-23 include all c files
2025-12-23 shorter
2025-12-23 reversed
2025-12-23 next attempt
2025-12-23 "constants"
2025-12-23 long beep lol
2025-12-23 longer
2025-12-23 something weird
2025-12-24 invalid note
2025-12-24 calibrated to roughly a second
2025-12-26 rm temp files
2025-12-26 new track
2025-12-26 turn on note
2025-12-26 order
2025-12-26 struct again
2025-12-26 missing notes?
2025-12-26 save a byte per note
2025-12-26 working in emu
2025-12-27 set and play
2026-01-04 sakura sakura
2026-01-04 lyrics
2026-01-04 echo test
2026-01-11 cleanup
2026-01-11 int55-75
2026-01-11 interrupts
2026-01-11 timers
2026-01-11 use timer3 for timing
2026-01-12 del old
2026-01-12 counter
2026-01-12 Revise IO port table in README.md
    Updated IO port descriptions for clarity.
2026-01-12 track function
2026-01-12 buttons
2026-01-12 header clean
2026-01-13 fix warnings because of brackets
2026-01-13 stop flashing
2026-01-13 move code into file
2026-01-13 snake case
2026-01-13 please dont stop the music
2026-01-13 chill
2026-01-13 indiactor
2026-01-13 serie
2026-01-13 sort for build
2026-01-13 sort other
2026-01-14 add menu with keys
2026-01-15 rtc struct
2026-01-15 rtc menu
2026-01-15 no ascii here
2026-01-15 swap
2026-01-15 less delays
2026-01-15 fix CI build interrupts
2026-01-15 build scripts
2026-01-15 time
2026-01-15 space
2026-01-15 return button
2026-01-15 update display from int75
2026-01-15 refresh function
2026-01-15 proto
2026-01-15 blinky
2026-01-15 date menu
2026-01-15 rtc address
2026-01-15 move to 2 and 3
2026-01-15 blink external
2026-01-15 time set
2026-01-15 lamp test 7
2026-01-16 bigger
2026-01-16 init menu item
2026-01-16 clamping
2026-01-16 rtc type beat
2026-01-16 view time
2026-01-16 undo
2026-01-16 nibble
2026-01-16 rtc ab
2026-01-16 update time in edit mode
2026-01-16 button indicators
2026-01-20 countup
2026-01-20 label formen
2026-02-08 deutsch
2026-02-08 bild entfernt
2026-02-21 name
2026-02-21 bild
2026-02-21 moove
2026-02-21 old board io
2026-02-21 clock api
2026-02-21 build old rom
2026-02-21 pass
2026-02-22 init ppi
2026-02-22 rtc io
2026-02-22 memory
2026-02-22 stop reset loop
2026-02-22 build 3 variants
2026-02-22 shortcuts
2026-04-11 diode gedreht
2026-04-11 rand rechts
2026-04-12 issues
2026-04-12 fix some issues, still broken
2026-04-12 board name
2026-04-12 safe
2026-04-13 inputs dont work
2026-04-13 ei is in the handler
2026-04-13 size
2026-04-13 no timer3 for now
2026-04-13 unfuck in emulator
2026-04-14 emulador
2026-04-14 GUTEN MORGEN
2026-04-15 emulator fixed
2026-04-15 schottky
2026-04-15 erc,drc
2026-04-16 values
2026-04-19 grosser ram
2026-04-19 doppelkondensator
2026-05-29 dont remove the one i just built
2026-05-31 truncate built roms
2026-06-12 3d models
2026-06-12 maschine
2026-06-12 bugfix
2026-06-12 space save
2026-06-12 debounce
2026-06-12 debounc 1
2026-06-12 timer test
2026-06-13 cancel
2026-06-13 pio test
2026-06-13 more tests
2026-06-16 motor1
2026-06-16 wheel test
2026-06-17 coin capture
2026-06-25 Diagramm
